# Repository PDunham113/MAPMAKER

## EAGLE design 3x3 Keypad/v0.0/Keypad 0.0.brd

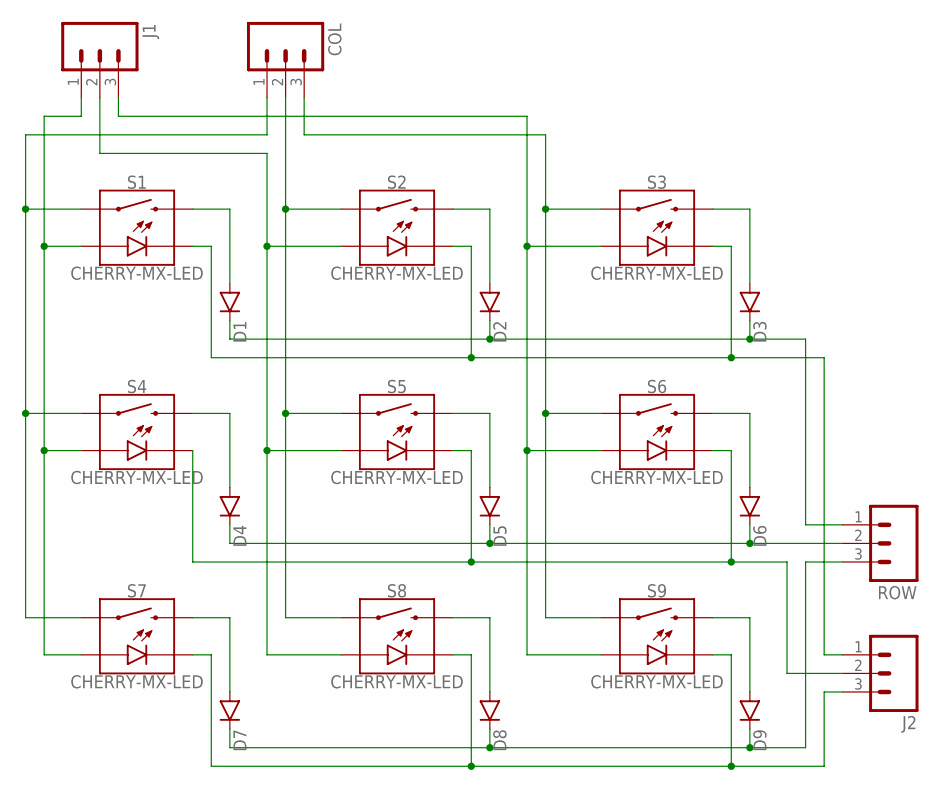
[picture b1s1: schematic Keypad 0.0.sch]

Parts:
COL: M03LOCK; 1X03_LOCK
D1, D2, D3, D4, D5, D6, D7, D8, D9: DIODESOT23; SOT23-3
J1, J2: M03LOCK; 1X03_LOCK
ROW: M03LOCK; 1X03_LOCK
S1, S2, S3, S4, S5, S6, S7, S8, S9: CHERRY-MX-LED

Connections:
unnamed: COL.1, S1.S1, S4.S1, S7.S1
unnamed: COL.2, S2.S1, S5.S1, S8.S1
unnamed: COL.3, S3.S1, S6.S1, S9.S1
unnamed: D1.3 (C), D2.3 (C), D3.3 (C), ROW.1
unnamed: D4.3 (C), D5.3 (C), D6.3 (C), ROW.2
unnamed: D7.3 (C), D8.3 (C), D9.3 (C), ROW.3
unnamed: D1.1 (A), S1.S2
unnamed: D2.1 (A), S2.S2
unnamed: D3.1 (A), S3.S2
unnamed: D4.1 (A), S4.S2
unnamed: D5.1 (A), S5.S2
unnamed: D6.1 (A), S6.S2
unnamed: D7.1 (A), S7.S2
unnamed: D8.1 (A), S8.S2
unnamed: D9.1 (A), S9.S2
unnamed: J1.1, S1.A, S4.A, S7.A
unnamed: J1.2, S2.A, S5.A, S8.A
unnamed: J1.3, S3.A, S6.A, S9.A
unnamed: J2.1, S1.K (C), S2.K (C), S3.K (C)
unnamed: J2.2, S4.K (C), S5.K (C), S6.K (C)
unnamed: J2.3, S7.K (C), S8.K (C), S9.K (C)

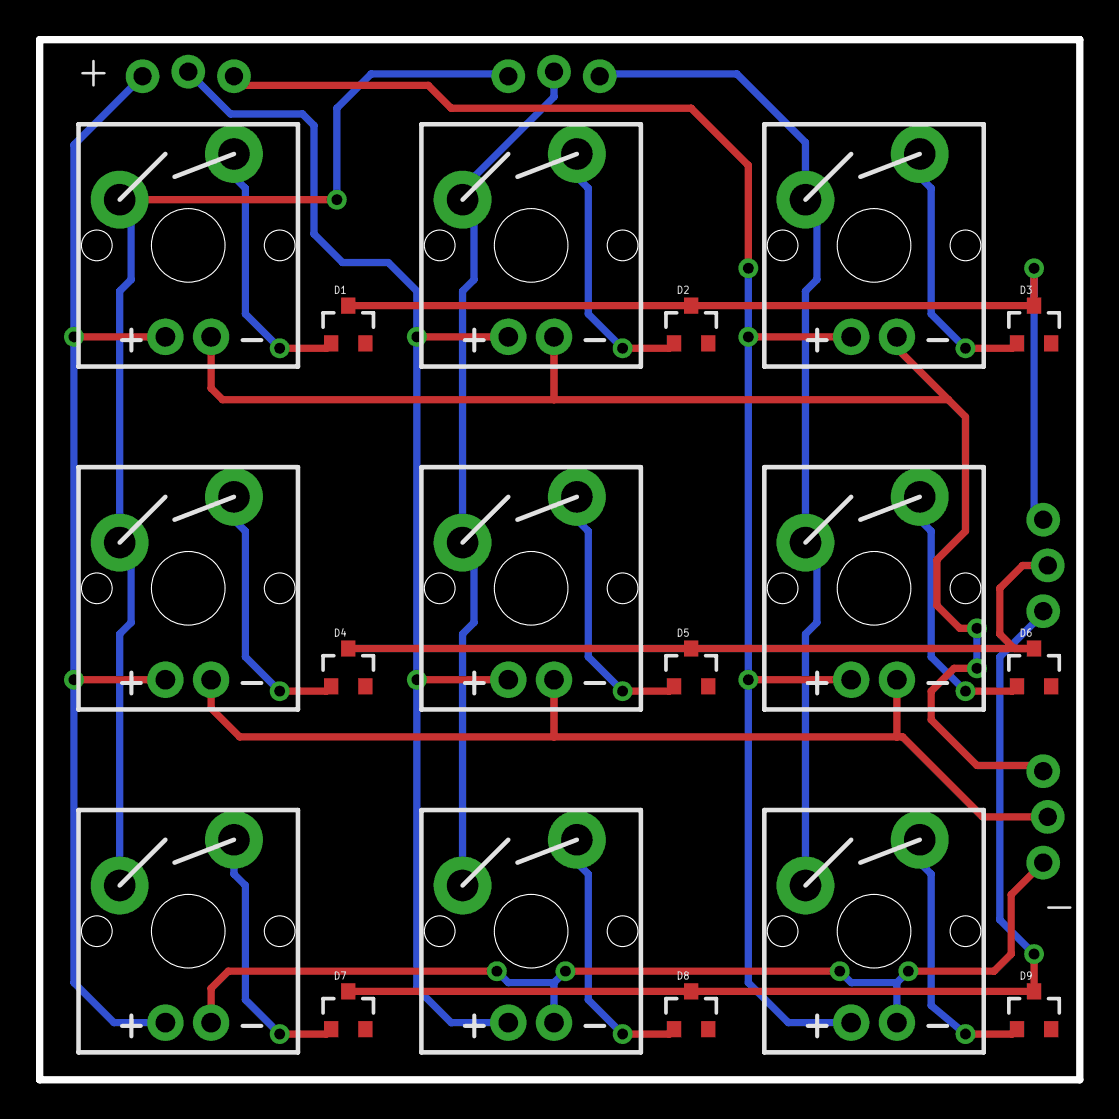
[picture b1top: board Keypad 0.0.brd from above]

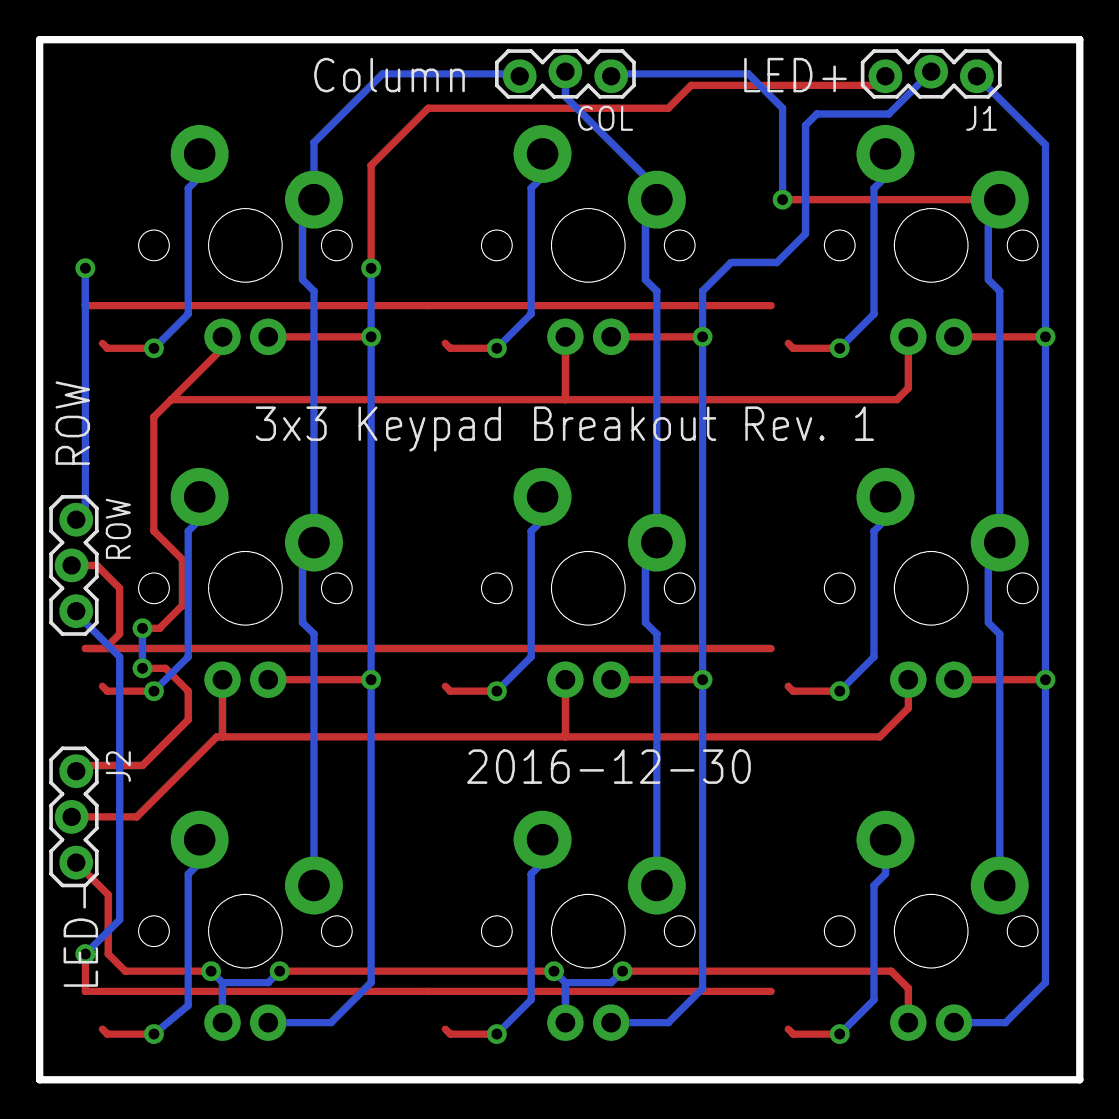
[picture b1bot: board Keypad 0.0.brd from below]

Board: 2 copper layers, 57.8 x 57.8 mm, 22 parts (4 on the bottom side), 21 nets.

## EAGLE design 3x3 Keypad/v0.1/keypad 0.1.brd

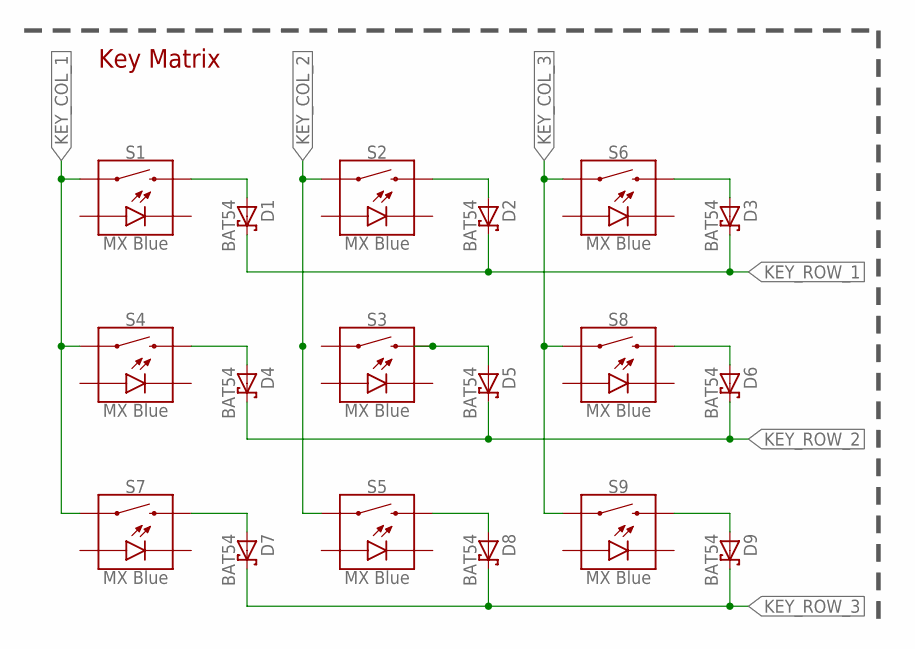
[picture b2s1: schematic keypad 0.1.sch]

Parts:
D1, D2, D3, D4, D5, D6, D7, D8, D9: BAT54; SOT23
S1, S2, S3, S4, S5, S6, S7, S8, S9: MX Blue; CHERRY-MX-LED

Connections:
KEY_COL_1: S1.S1 (1), S4.S1 (1), S7.S1 (1)
KEY_COL_2: S2.S1 (1), S5.S1 (1)
KEY_COL_3: S6.S1 (1), S8.S1 (1), S9.S1 (1)
KEY_ROW_1: D1.3 (C), D2.3 (C), D3.3 (C)
KEY_ROW_2: D4.3 (C), D5.3 (C), D6.3 (C)
KEY_ROW_3: D7.3 (C), D8.3 (C), D9.3 (C)
unnamed: D1.1 (A), S1.S2 (2)
unnamed: D4.1 (A), S4.S2 (2)
unnamed: D7.1 (A), S7.S2 (2)
unnamed: D8.1 (A), S5.S2 (2)
unnamed: D5.1 (A), S3.S2 (2)
unnamed: D2.1 (A), S2.S2 (2)
unnamed: D3.1 (A), S6.S2 (2)
unnamed: D6.1 (A), S8.S2 (2)
unnamed: D9.1 (A), S9.S2 (2)

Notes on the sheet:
Key Matrix

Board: 2 copper layers, 18 parts (0 on the bottom side), 15 nets, no tracks yet.

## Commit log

2018-01-10 Initial Commit
    Added existing files

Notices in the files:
parts and their libraries:
SparkFun-Electromechanical: Licensing: Creative Commons ShareAlike 4.0 International - https://creativecommons.org/licenses/by-sa/4.0
